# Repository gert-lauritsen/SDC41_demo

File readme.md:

# 🌿 SCD41_D_R2 Demo for ESP32-WROOM (Arduino)

Dette projekt demonstrerer, hvordan man bruger **Sensirion SCD41-D-R2** til at måle **CO₂**, **temperatur** og **relativ fugtighed** med et **ESP32-WROOM** udviklingsboard i **Arduino**.

## 🔌 Hardware (I²C forbindelse)
| SCD41 pin | ESP32 pin | Funktion |
|-----------|-----------|----------|
| VDD       | 3V3       | Forsyning |
| GND       | GND       | Jord |
| SDA       | GPIO21    | I²C Data |
| SCL       | GPIO22    | I²C Clock |

> Du kan vælge andre pins, men husk at ændre `Wire.begin(SDA, SCL)` i koden.

## 🧰 Software
- **Arduino IDE v2.x** eller **PlatformIO**
- **ESP32 by Espressif Systems** (Boards Manager)
- Bibliotek: **Sensirion I2C SCD4x** (Library Manager)

## 🚀 Kom i gang
1. Åbn mappen i Arduino IDE og vælg board **ESP32 Dev Module**.
2. Installer biblioteket **Sensirion I2C SCD4x**.
3. Tilslut sensoren som angivet ovenfor.
4. Upload `SCD41_ESP32_Arduino_Demo.ino` og åbn Serial Monitor @ **115200 baud**.
5. Skriv `h` + Enter for hjælpetekst/kommandoer.

## 🎛️ Seriel kommando-menu
- `h` — hjælp
- `start` / `stop` — start/stop måling
- `reinit` — software re-init
- `selftest` — kør intern selvtest
- `abc on` / `abc off` — Automatic Baseline Correction til/fra
- `alt <meter>` — sæt sensorhøjde, fx `alt 45`
- `press <mbar>` — sæt omgivende tryk, fx `press 1013`

## 🧪 Forventet output
```
SCD41-D-R2 Demo - ESP32-WROOM (Arduino)
I2C: SDA=21, SCL=22
Sensor SN: 1234-5678-9ABC
[OK] Measurement started
CO2: 413 ppm | Temp: 23.7 °C | RH: 44.6 %
...
```

## 📚 Referencer
- Sensirion SCD41-D-R2 datasheet
- Sensirion Arduino Library for SCD4x
- ESP32 Arduino Core Docs

## 👤 Forfatter
Gert Lauritsen — Fieldtest / Airborne Instruments

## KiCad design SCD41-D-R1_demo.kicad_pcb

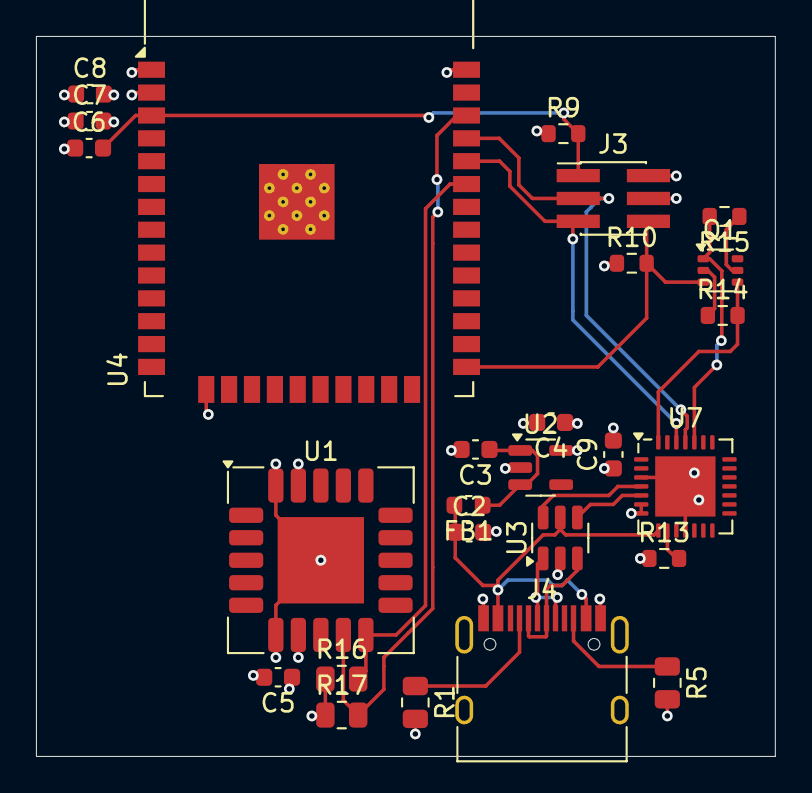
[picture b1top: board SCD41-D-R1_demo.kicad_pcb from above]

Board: 4 copper layers, 41.1 x 40.0 mm, 26 parts (0 on the bottom side), 21 nets.

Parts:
C2: 10nF; C_0603_1608Metric
C3, C4, C5: 1uF; C_0603_1608Metric
C6, C7, C8: 0.1uf; C_0603_1608Metric
C9: 10u; C_0603_1608Metric
FB1: Ferrite Bead; L_0603_1608Metric
J3: Prog; PinHeader_2x03_P1.27mm_Vertical_SMD
J4: USB_C_Receptacle; USB_C_Receptacle_HRO_TYPE-C-31-M-12
Q1: BC846BS; SOT-363_SC-70-6
R1, R5: 5k1; R_0805_2012Metric
R9, R10: 10K; R_0603_1608Metric
R13: 1k; R_0603_1608Metric
R14, R15: 10k; R_0603_1608Metric
R16, R17: 10k; R_0805_2012Metric
U1: SCD41-D-R2; Sensirion_SCD4x-1EP_10.1x10.1mm_P1.25mm_EP4.8x4.8mm
U2: AP2112K-3.3; SOT-23-5
U3: USBLC6-2SC6; SOT-23-6
U4: ESP32-WROOM-32
U7: CP2102N-Axx-xQFN28; QFN-28-1EP_5x5mm_P0.5mm_EP3.35x3.35mm

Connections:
+3.3V: C4.1, C5.1, C7.2, C8.2, C9.1, J3.2, R9.1, R10.1, R13.1, R16.1, R17.1, U1.7 (VDD), U1.19 (VDD), U2.5 (VOUT), U4.2 (VDD), U7.6 (VDD), U7.7 (VREGIN)
BT: J3.6, Q1.3 (C2), R10.2, U4.25 (IO0)
D+: J4.A6 (D+), J4.B6 (D+), U3.1 (I/O1)
D-: J4.A7 (D-), J4.B7 (D-), U3.3 (I/O2)
EN: C6.2, J3.1, R9.2, U4.3 (EN)
GND: C2.2, C3.2, C4.2, C5.2, C6.1, C7.1, C8.1, C9.2, J3.4, J4.A1 (GND), J4.A12 (GND), J4.B1 (GND), J4.B12 (GND), J4.S1 (SHIELD), R1.2, R5.2, U1.6 (GND), U1.20 (GND), U1.21 (GND), U2.2 (GND), U3.2 (GND), U4.1 (GND), U4.15 (GND), U4.38 (GND), U4.39 (GND), U7.3 (GND), U7.11 (~SUSPEND), U7.29 (GND)
unnamed: J4.A5 (CC1), R1.1
unnamed: J4.B5 (CC2), R5.1
unnamed: Q1.2 (B1), R14.1
unnamed: Q1.1 (E1), R15.2, U7.24 (~RTS)
unnamed: Q1.5 (B2), R15.1
unnamed: Q1.4 (E2), R14.2, U7.28 (~DTR)
unnamed: C3.1, FB1.1, U2.1 (VIN), U2.3 (EN)
unnamed: R13.2, U7.9 (~RST)
RX: J3.5, U4.34 (RXD0/IO3), U7.26 (TXD)
SCL: R17.2, U1.9 (SCL), U4.36 (IO22)
SDA: R16.2, U1.10 (SDA), U4.33 (IO21)
TX: J3.3, U4.35 (TXD0/IO1), U7.25 (RXD)
USBN: U3.4 (I/O2), U7.5 (D-)
USBP: U3.6 (I/O1), U7.4 (D+)
VIN: C2.1, FB1.2, J4.A4 (VBUS), J4.A9 (VBUS), J4.B4 (VBUS), J4.B9 (VBUS), U3.5 (VBUS), U7.8 (VBUS)

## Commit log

2025-11-10 init
2025-11-10 programmer
2025-11-10 usb-c
2025-11-10 usbc
2025-11-26 Initial commit - SCD41 Matter sensor
2025-11-28 layout
